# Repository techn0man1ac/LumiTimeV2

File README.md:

Attention, the project is under development, so it is subject to change.

# LumiTimeV2

LumiTimeV2 - this is the "Perpetual" Wristwatch(project code name "LumiTimeV2") with 12 red LEDs, it have LIR3032 Li-Ion battery and 12 solar cells, based on a Microchip microcontroller ATmega328P. It's full open source(firmware and hardware).

Next generation wristwatch after [12 LED ATtiny "Perpetual" Wristwatch](https://github.com/techn0man1ac/PerpetualLEDWristwatch). 

# Video demonstration:

/* Link may be here */

# How it's work?

/* Description may be here */

# How to set the time?

/* Description may be here */

# 3D model PCB:

The board is two-layer, with components on both sides. 

## PCB front view

On the front side of the board there are 12 microsolar panels in a circle and 12 red LEDs that display the time and the RTC with its quartz resonator:

## Back view

In the center of the board is the ATmega328 microcontroller(like Arduino Nano). Under LED III is a button used to display and set the time for the watch. All passive components of the circuit are of 0805 size, which allows them to be soldered without additional soldering equipment:

PCB have 35 mm in the diameter:

The thickness of the board is recommended to take 0.8mm otherwise it may not fit into the case.

# PCB gerber files:

Files for fabrication:

https://github.com/techn0man1ac/LumiTimeV2/tree/main/LumiTimeV2/PCB/Gerbers

# 3D model of PCB 

3D model in STEP format:

https://github.com/techn0man1ac/LumiTimeV2/tree/main/LumiTimeV2/PCB/3dModel

# Schematic

The circuitry of the clock provides for a sufficient number of parts, due to which the board is required to have parts on both sides. Here is a detailed description of each block on the schematic.

## Charging system

The project uses 12 photodiodes BPW34S(PV array) that work like miniature solar panels, whose function is to charge the battery from light. 
The charging circuit is very primitive, since each micro-solar panel generates ~0.5V, if they are all 12 connected in series, the total voltage will be around 6 V, protect to overcharge the battery,used ZD1 Zener diode(4.7V), and a diode D13 is also prevent to reverse current(current flow into the solar panels) and add drop voltage 0.6-0.7V, as a result, we have a battery charging system with voltage like 4.0..4.1V. Charging current on a sunny day is ~2 mA.

## Battery

/* Description may be here */

## LEDs matrix

/* Description may be here */

## RTC

/* Description may be here */

## Programming connector

/* Description may be here */

## Microcontroller

/* Description may be here */

# Our mission and vision

It has a mission and vision that it borrowed from the [previous version](https://github.com/techn0man1ac/PerpetualLEDWristwatch) and carries the same values, such as:

## Mission:

To develop a simply and eco-friendly watch that integrates innovative technologies with minimal components, ensuring energy efficiency is within reach for all.

## Vision:

We aim to achieve a world where energy-saving technology is accessible to everyone, where our watch serves as a symbol of environmental stewardship and innovative solutions in energy efficiency.

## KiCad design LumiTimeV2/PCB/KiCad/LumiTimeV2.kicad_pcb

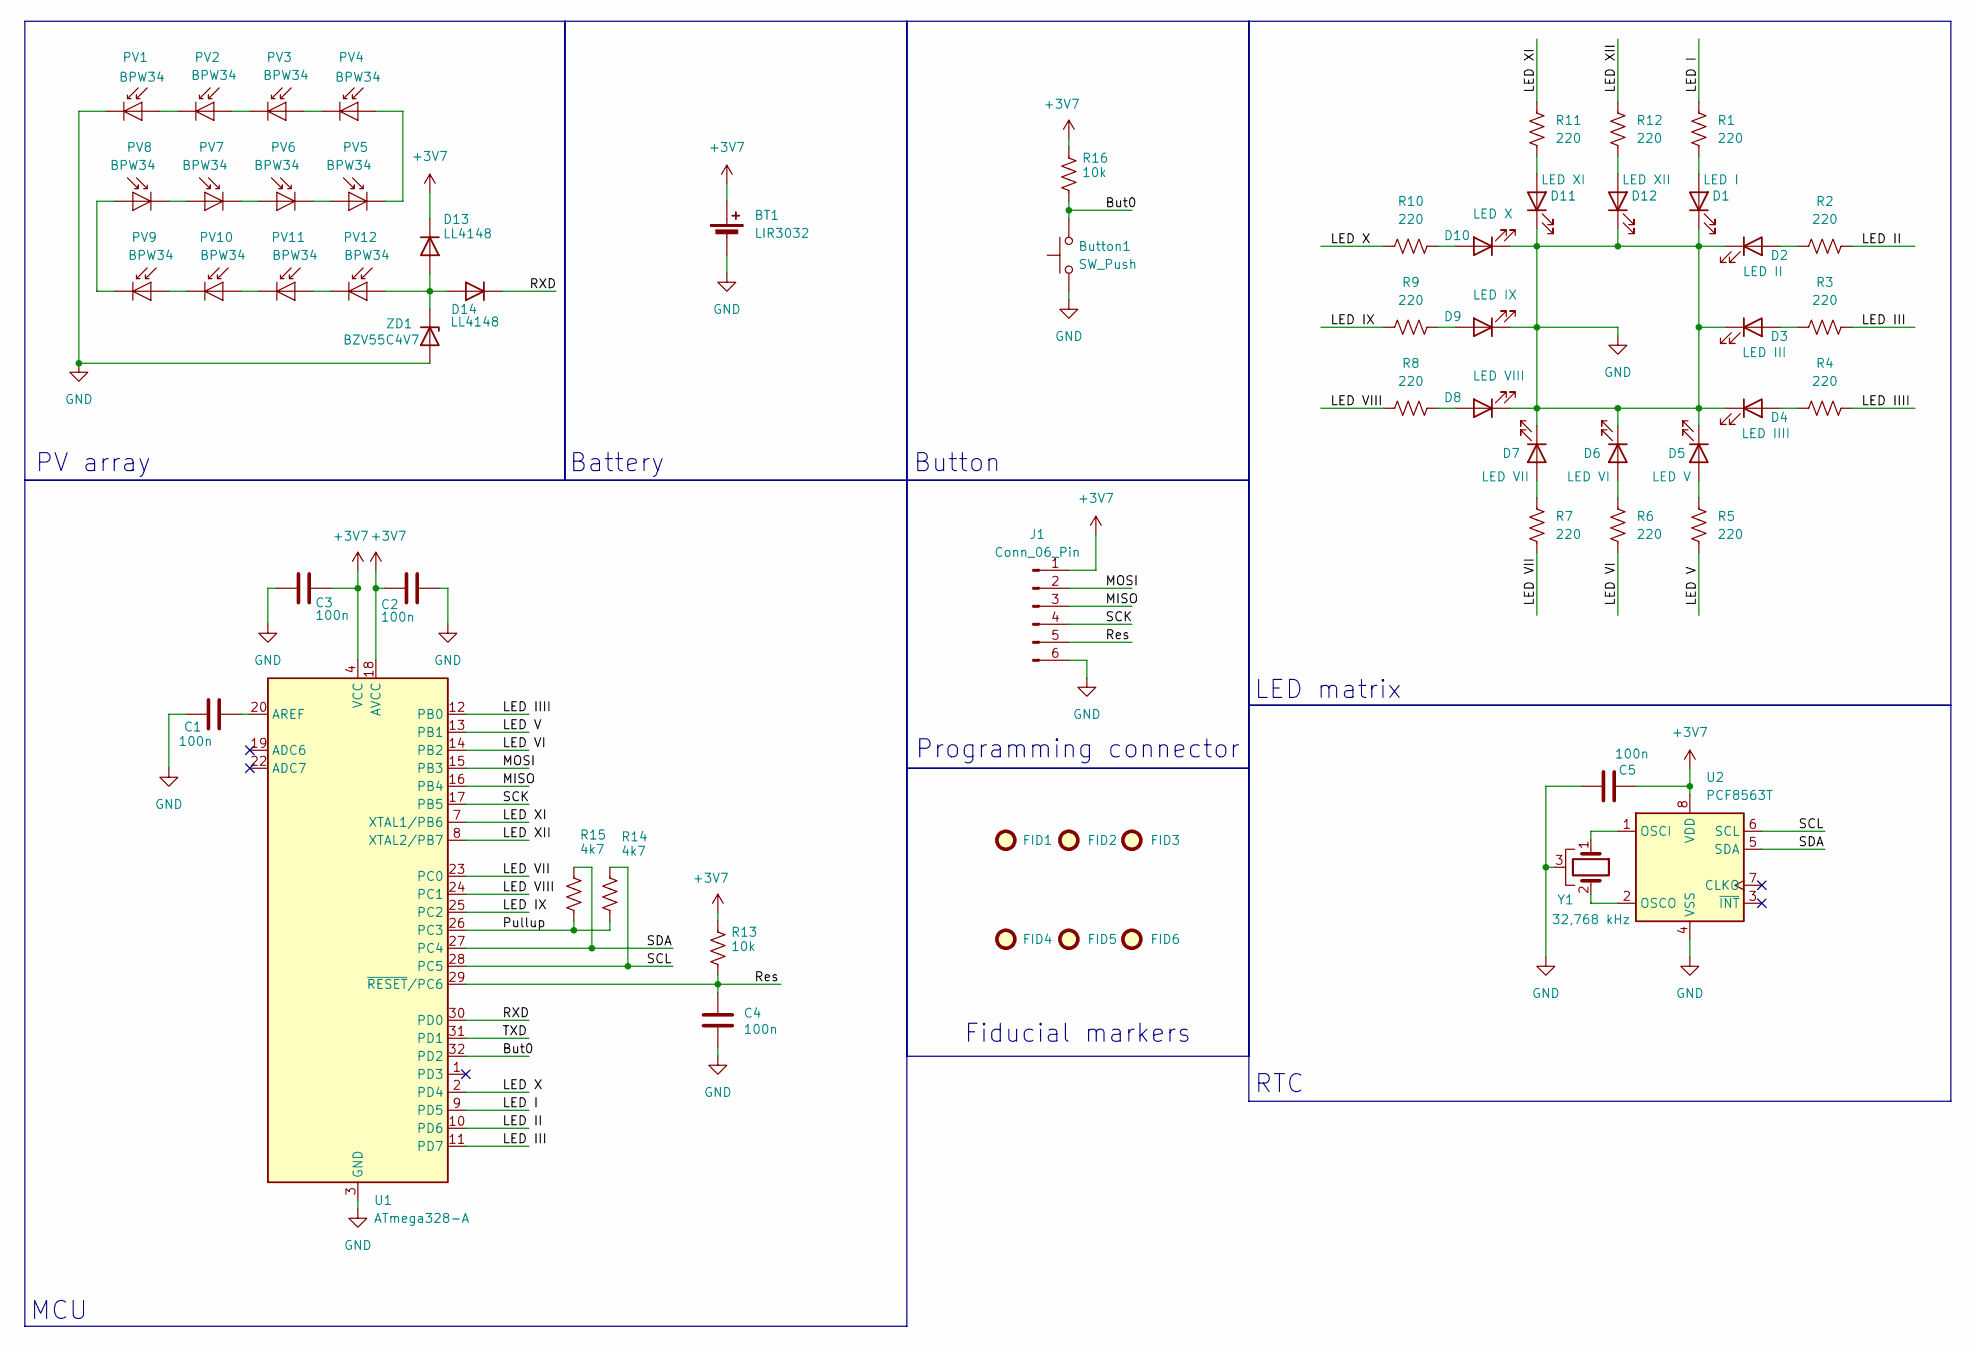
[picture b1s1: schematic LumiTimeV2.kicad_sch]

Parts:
BT1: LIR3032
Button1: SW_Push; SW_SPST_FSMSM
C1, C2, C3, C4, C5: 100n; C_0805_2012Metric
D1: LED I; LED_0805_2012Metric
D2: LED II; LED_0805_2012Metric
D3: LED III; LED_0805_2012Metric
D4: LED IIII; LED_0805_2012Metric
D5: LED V; LED_0805_2012Metric
D6: LED VI; LED_0805_2012Metric
D7: LED VII; LED_0805_2012Metric
D8: LED VIII; LED_0805_2012Metric
D9: LED IX; LED_0805_2012Metric
D10: LED X; LED_0805_2012Metric
D11: LED XI; LED_0805_2012Metric
D12: LED XII; LED_0805_2012Metric
D13, D14: LL4148; D_MiniMELF
FID1, FID2, FID3, FID4, FID5, FID6: Fiducial; Fiducial_0.5mm_Mask1mm
J1: Conn_06_Pin; PinHeader_1x06_P1.00mm_Vertical_SMD_Pin1Right
PV1, PV2, PV3, PV4, PV5, PV6, PV7, PV8, PV9, PV10, PV11, PV12: BPW34; Osram_BPW34S-SMD
R1, R2, R3, R4, R5, R6, R7, R8, R9, R10, R11, R12: 220; R_0805_2012Metric
R13, R16: 10k; R_0805_2012Metric
R14, R15: 4k7; R_0805_2012Metric
U1: ATmega328-A; TQFP-32_7x7mm_P0.8mm
U2: PCF8563T; SOIC-8_3.9x4.9mm_P1.27mm
Y1: 32,768 kHz; Crystal_SMD_MicroCrystal_MS3V-T1R
ZD1: BZV55C4V7; D_MiniMELF

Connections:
+3V7: BT1.1 (+), C2.1, C3.1, C5.1, D13.1 (K), J1.1, R13.1, R16.1, U1.4 (VCC), U1.6 (VCC), U1.18 (AVCC), U2.8 (VDD)
/But0: Button1.2, R16.2, U1.32 (PD2)
/LED I: R1.1, U1.9 (PD5)
/LED II: R2.2, U1.10 (PD6)
/LED III: R3.2, U1.11 (PD7)
/LED IIII: R4.2, U1.12 (PB0)
/LED IX: R9.1, U1.25 (PC2)
/LED V: R5.2, U1.13 (PB1)
/LED VI: R6.2, U1.14 (PB2)
/LED VII: R7.2, U1.23 (PC0)
/LED VIII: R8.1, U1.24 (PC1)
/LED X: R10.1, U1.2 (PD4)
/LED XI: R11.1, U1.7 (XTAL1/PB6)
/LED XII: R12.1, U1.8 (XTAL2/PB7)
/MISO: J1.3, U1.16 (PB4)
/MOSI: J1.2, U1.15 (PB3)
/Pullup: R14.2, R15.2, U1.26 (PC3)
/RXD: D14.1 (K), U1.30 (PD0)
/Res: C4.1, J1.5, R13.2, U1.29 (~RESET/PC6)
/SCK: J1.4, U1.17 (PB5)
/SCL: R14.1, U1.28 (PC5), U2.6 (SCL)
/SDA: R15.1, U1.27 (PC4), U2.5 (SDA)
/TXD: U1.31 (PD1)
GND: BT1.2 (-), Button1.1, C1.2, C2.2, C3.2, C4.2, C5.2, D1.1 (K), D2.1 (K), D3.1 (K), D4.1 (K), D5.1 (K), D6.1 (K), D7.1 (K), D8.1 (K), D9.1 (K), D10.1 (K), D11.1 (K), D12.1 (K), J1.6, PV1.1 (K), U1.3 (GND), U1.5 (GND), U1.21 (GND), U2.4 (VSS), Y1.3, ZD1.2 (A)
unnamed: D1.2 (A), R1.2
unnamed: D2.2 (A), R2.1
unnamed: D3.2 (A), R3.1
unnamed: D4.2 (A), R4.1
unnamed: D5.2 (A), R5.1
unnamed: D6.2 (A), R6.1
unnamed: D7.2 (A), R7.1
unnamed: D8.2 (A), R8.2
unnamed: D9.2 (A), R9.2
unnamed: D10.2 (A), R10.2
unnamed: D11.2 (A), R11.2
unnamed: D12.2 (A), R12.2
unnamed: D13.2 (A), D14.2 (A), PV12.2 (A), ZD1.1 (K)
unnamed: PV1.2 (A), PV2.1 (K)
unnamed: PV2.2 (A), PV3.1 (K)
unnamed: PV3.2 (A), PV4.1 (K)
unnamed: PV4.2 (A), PV5.1 (K)
unnamed: PV5.2 (A), PV6.1 (K)
unnamed: PV6.2 (A), PV7.1 (K)
unnamed: PV7.2 (A), PV8.1 (K)
unnamed: PV8.2 (A), PV9.1 (K)
unnamed: PV10.2 (A), PV11.1 (K)
unnamed: PV9.2 (A), PV10.1 (K)
unnamed: PV11.2 (A), PV12.1 (K)
unnamed: C1.1, U1.20 (AREF)
unnamed: U2.1 (OSCI), Y1.1
unnamed: U2.2 (OSCO), Y1.2

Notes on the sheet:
MCU
LED matrix
Programming connector
Battery
Button
RTC
PV array
Fiducial markers

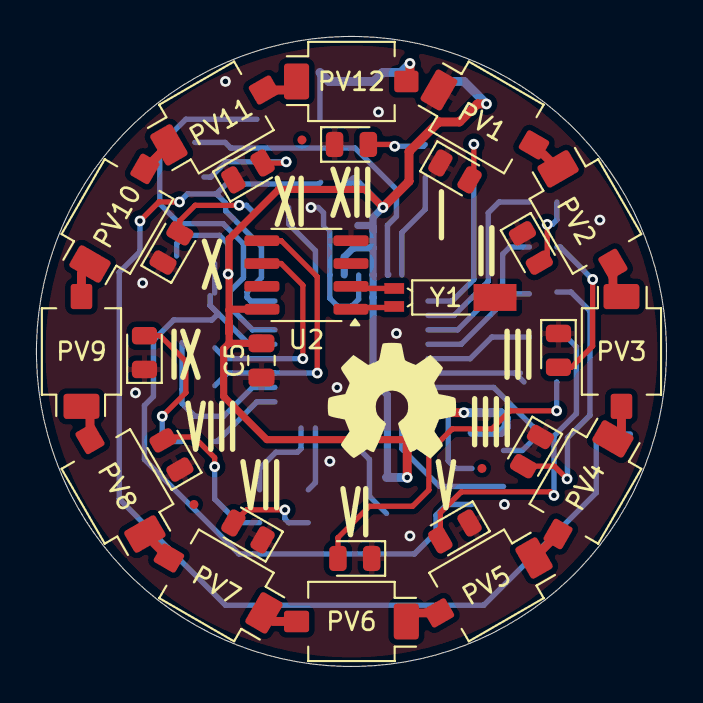
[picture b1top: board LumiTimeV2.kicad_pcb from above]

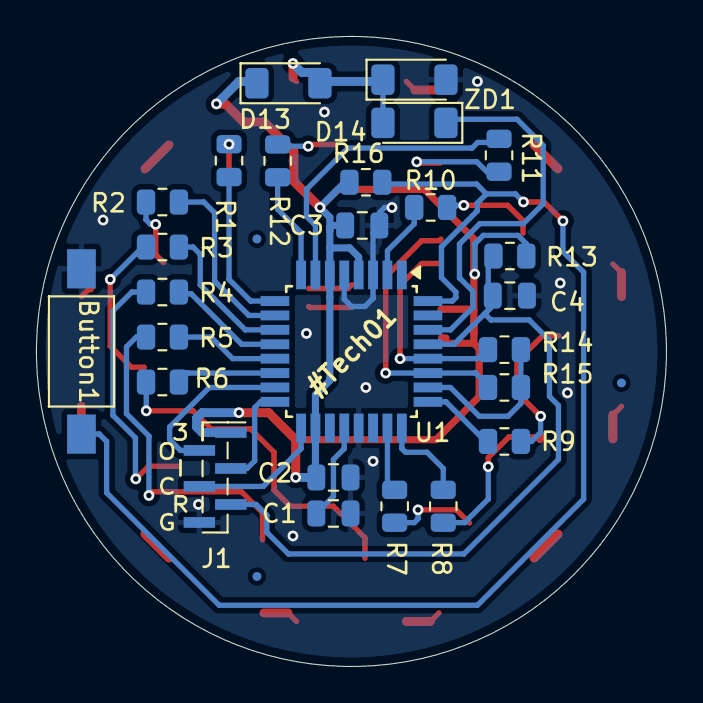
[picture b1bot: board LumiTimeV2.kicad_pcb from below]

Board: 2 copper layers, 35.0 x 35.0 mm, 60 parts (29 on the bottom side), 50 nets.

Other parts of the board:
OSHW: LOGO

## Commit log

2024-12-16 Change#000
2024-12-16 Change#000
    Add first project files
2024-12-20 Change#00
    Add project KiCad files
2024-12-20 Change#001
    Add some details
2024-12-20 Change#003
    Add PCB board render
2024-12-20 Change#004
    Add some stuff
2025-01-13 Change#004
    Delete files
2025-01-14 Change#005
    Add fresh project files
2025-01-14 Change#005
    Cosmetics
2025-01-14 Change#005
    trash
2025-01-14 Change#005
    Delete PCB/KiCad/LumiTimeV2.kicad_prl
2025-01-14 Change#006
    Update README.md
2025-01-14 Change#005
    2024->2025
2025-01-15 Change#005
    Delete PCB directory
2025-01-15 Change#006
    Delete img directory
2025-01-15 Change#006
    Add new files - final PCB version
2025-01-15 Change#006
    Delete PCB/3dModel/LumiTimeV2PCB.stl
2025-01-18 Change#007
    Some new ideas
2025-01-18 Change#007
    35.00 -> 35.0
2025-01-18 Change#007
    Attention!
2025-01-19 Change#008
    Delete PCB directory
2025-01-19 Change#008
    Delete img directory
2025-01-19 Change#008
    Add new files in "LumiTimeV2" catalog
2025-01-19 Change#008
    Add more descriptions
2025-01-19 Change#008
    Cosmetics
2025-01-19 Change#008
    Delete LumiTimeV2/PCB/KiCad/fp-info-cache
2025-01-19 Change#008
    Delete LumiTimeV2/PCB/KiCad/LumiTimeV2.kicad_prl
2025-01-19 Change#008
    Fresh
2025-01-19 Change#008
    Add open-source hardware logo
2025-01-19 Change#008
    Add OSHW logo
2025-01-19 Change#008
    Rename Schematic.png to LumiTimeV2Schematic.png
2025-01-19 Change#008
    Cosmetic
2025-01-19 Change#008
    New gerber files
2025-01-19 Change#009
    Cosmetics
2025-01-19 Change#009
    D14 -> D13
2025-03-16 Change#010
    Add fiducial markers to PCB
